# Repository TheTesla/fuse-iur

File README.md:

# Electronic fuse: U, I

This small board protects devices against power faults:

* Reverse polarity of the power source
* Overvoltage
* Overcurrent

Features:

* Bidirectional
* Power consumption: < 1 µA
* Absolute maximum voltage between all pins: 60 V

## Author

Stefan Helmert <stefan@entrsoerv.de>

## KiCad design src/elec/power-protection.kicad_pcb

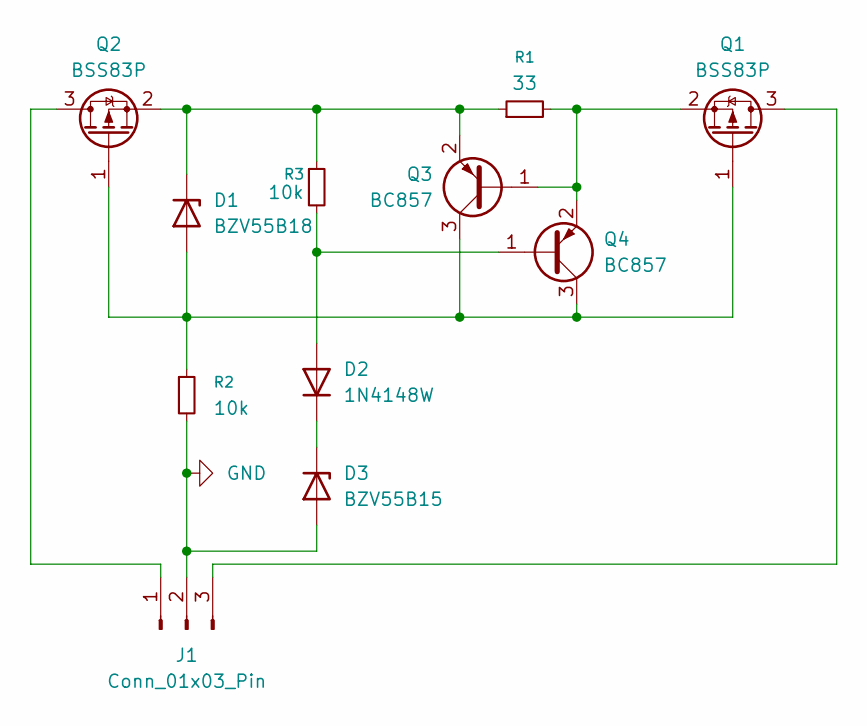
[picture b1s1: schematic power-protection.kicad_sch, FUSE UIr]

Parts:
D1: BZV55B18; D_MiniMELF
D2: 1N4148W; D_SOD-123
D3: BZV55B15; D_MiniMELF
J1: Conn_01x03_Pin; PinHeader_1x03_P2.54mm_Vertical
Q1, Q2: BSS83P; SOT-23
Q3, Q4: BC857; SOT-23
R1: 33; R_0805_2012Metric
R2, R3: 10k; R_0805_2012Metric

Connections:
GND: D3.2 (A), J1.2, R2.2
unnamed: D1.2 (A), Q1.1 (G), Q2.1 (G), Q3.3 (C), Q4.3 (C), R2.1
unnamed: D1.1 (K), Q2.2 (S), Q3.2 (E), R1.1, R3.1
unnamed: D2.2 (A), Q4.1 (B), R3.2
unnamed: D2.1 (K), D3.1 (K)
unnamed: J1.1, Q2.3 (D)
unnamed: J1.3, Q1.3 (D)
unnamed: Q1.2 (S), Q3.1 (B), Q4.2 (E), R1.2

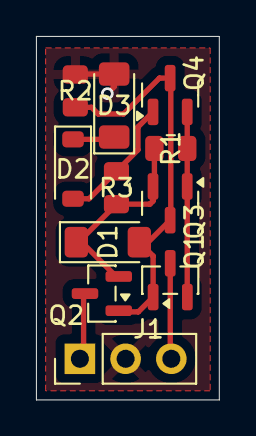
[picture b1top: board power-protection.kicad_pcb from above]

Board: 2 copper layers, 10.2 x 20.2 mm, 11 parts (0 on the bottom side), 8 nets.

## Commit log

2025-12-21 PCB ready
2026-01-03 Fix: wrong MOSFET (p channel needed); README.md added
2026-01-03 Simulation z-diode value according real design; started reuse
2026-01-06 started fixing
2026-01-06 simulate histeresis
